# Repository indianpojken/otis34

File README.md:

# Otis34

A minimalist, not so ergonomic 34-key keyboard designed for portability.
Features a unibody layout and support for Kailh Choc V1 low-profile switches via hotswap sockets and OLED.

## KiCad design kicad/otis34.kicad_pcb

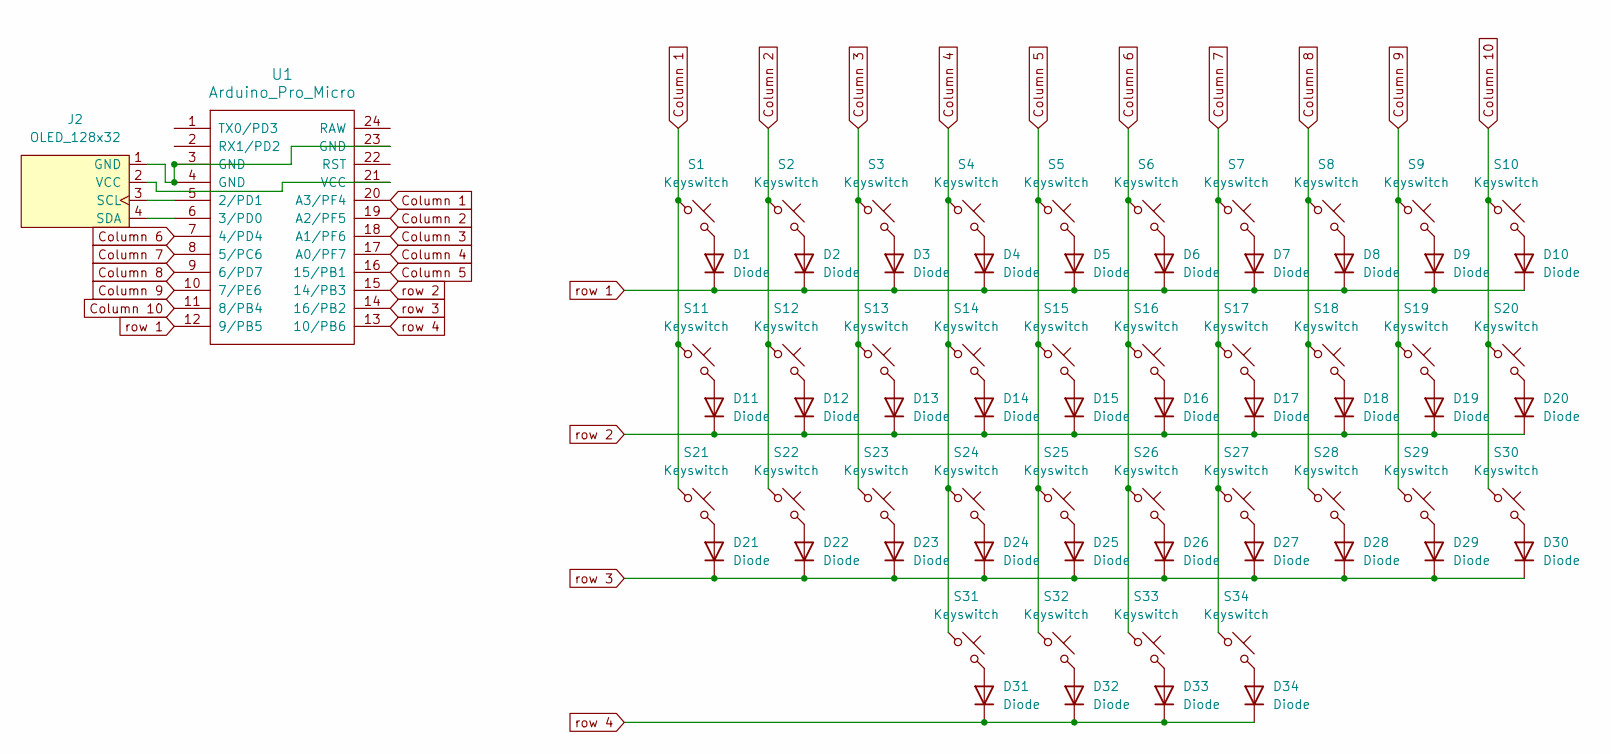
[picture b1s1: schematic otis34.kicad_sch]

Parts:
D1, D2, D3, D4, D5, D6, D7, D8, D9, D10, D11, D12, D13, D14, D15, D16, D17, D18, D19, D20, D21, D22, D23, D24, D25, D26, D27, D28, D29, D30, D31, D32, D33, D34: Diode; Diode_SOD-123
J2: OLED_128x32
S1, S2, S3, S4, S5, S6, S7, S8, S9, S10, S11, S12, S13, S14, S15, S16, S17, S18, S19, S20, S21, S22, S23, S24, S25, S26, S27, S28, S29, S30, S31, S32, S33, S34: Keyswitch; Hotswap_Choc_V1V2_1.00u
U1: Arduino_Pro_Micro

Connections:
Column 1: S1.1, S11.1, S21.1, U1.20 (A3/PF4)
Column 2: S2.1, S12.1, S22.1, U1.19 (A2/PF5)
Column 3: S3.1, S13.1, S23.1, U1.18 (A1/PF6)
Column 4: S4.1, S14.1, S24.1, S31.1, U1.17 (A0/PF7)
Column 5: S5.1, S15.1, S25.1, S32.1, U1.16 (15/PB1)
Column 6: S6.1, S16.1, S26.1, S33.1, U1.7 (4/PD4)
Column 7: S7.1, S17.1, S27.1, S34.1, U1.8 (5/PC6)
Column 8: S8.1, S18.1, S28.1, U1.9 (6/PD7)
Column 9: S9.1, S19.1, S29.1, U1.10 (7/PE6)
Column 10: S10.1, S20.1, S30.1, U1.11 (8/PB4)
unnamed: D1.2 (A), S1.2
unnamed: D2.2 (A), S2.2
unnamed: D3.2 (A), S3.2
unnamed: D4.2 (A), S4.2
unnamed: D5.2 (A), S5.2
unnamed: D6.2 (A), S6.2
unnamed: D7.2 (A), S7.2
unnamed: D8.2 (A), S8.2
unnamed: D9.2 (A), S9.2
unnamed: D10.2 (A), S10.2
unnamed: D11.2 (A), S11.2
unnamed: D12.2 (A), S12.2
unnamed: D13.2 (A), S13.2
unnamed: D14.2 (A), S14.2
unnamed: D15.2 (A), S15.2
unnamed: D16.2 (A), S16.2
unnamed: D17.2 (A), S17.2
unnamed: D18.2 (A), S18.2
unnamed: D19.2 (A), S19.2
unnamed: D20.2 (A), S20.2
unnamed: D21.2 (A), S21.2
unnamed: D22.2 (A), S22.2
unnamed: D23.2 (A), S23.2
unnamed: D24.2 (A), S24.2
unnamed: D25.2 (A), S25.2
unnamed: D26.2 (A), S26.2
unnamed: D27.2 (A), S27.2
unnamed: D28.2 (A), S28.2
unnamed: D29.2 (A), S29.2
unnamed: D30.2 (A), S30.2
unnamed: D31.2 (A), S31.2
unnamed: D32.2 (A), S32.2
unnamed: D33.2 (A), S33.2
unnamed: D34.2 (A), S34.2
unnamed: J2.1 (GND), U1.3 (GND), U1.4 (GND), U1.23 (GND)
unnamed: J2.3 (SCL), U1.5 (2/PD1)
unnamed: J2.4 (SDA), U1.6 (3/PD0)
unnamed: J2.2 (VCC), U1.21 (VCC)
row 1: D1.1 (K), D2.1 (K), D3.1 (K), D4.1 (K), D5.1 (K), D6.1 (K), D7.1 (K), D8.1 (K), D9.1 (K), D10.1 (K), U1.12 (9/PB5)
row 2: D11.1 (K), D12.1 (K), D13.1 (K), D14.1 (K), D15.1 (K), D16.1 (K), D17.1 (K), D18.1 (K), D19.1 (K), D20.1 (K), U1.15 (14/PB3)
row 3: D21.1 (K), D22.1 (K), D23.1 (K), D24.1 (K), D25.1 (K), D26.1 (K), D27.1 (K), D28.1 (K), D29.1 (K), D30.1 (K), U1.14 (16/PB2)
row 4: D31.1 (K), D32.1 (K), D33.1 (K), D34.1 (K), U1.13 (10/PB6)

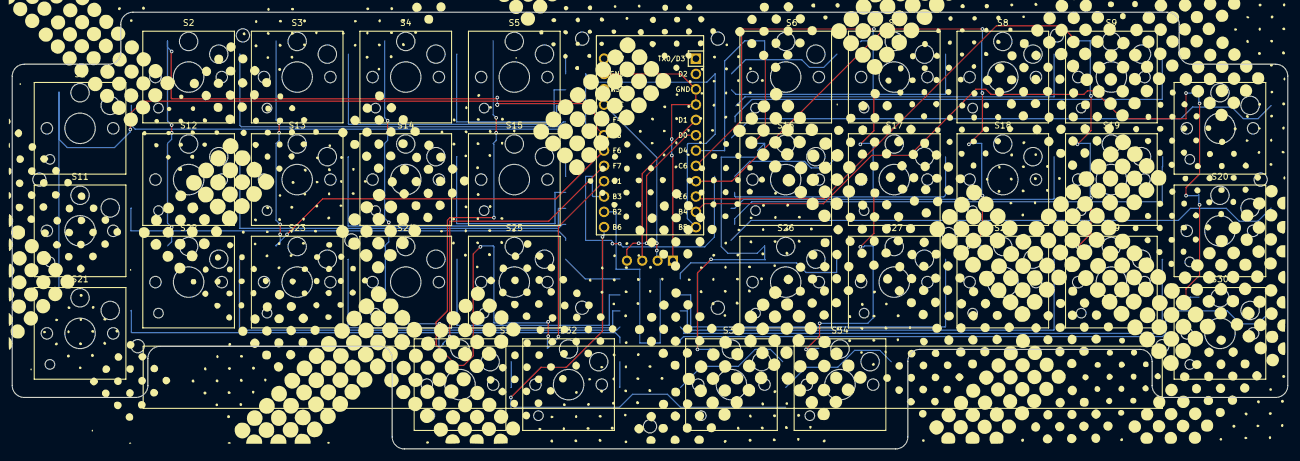
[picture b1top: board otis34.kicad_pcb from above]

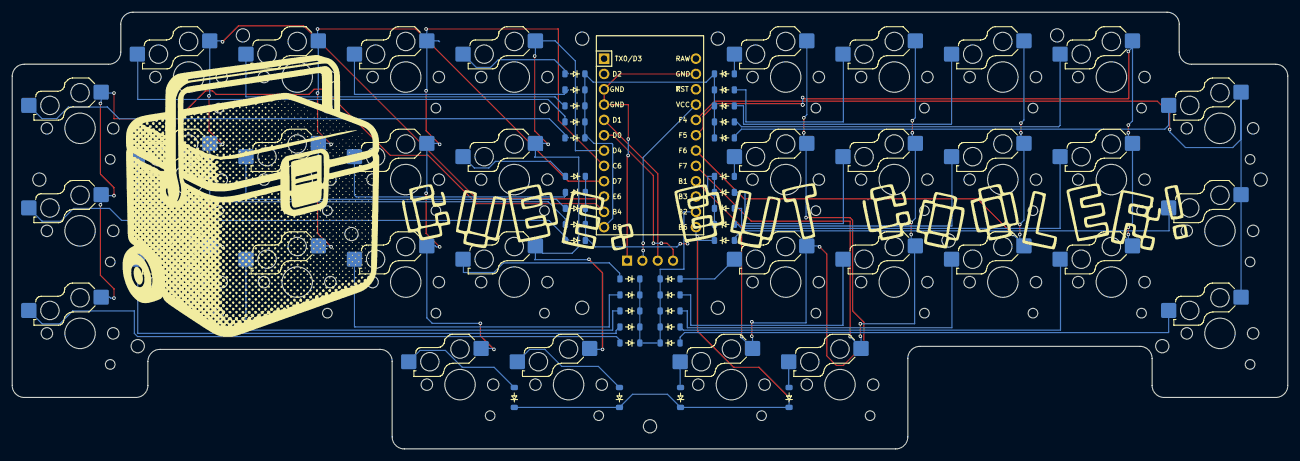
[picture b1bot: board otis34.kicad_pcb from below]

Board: 2 copper layers, 211.5 x 72.4 mm, 70 parts (35 on the bottom side), 52 nets.

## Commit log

2025-04-30 inital
2025-04-30 feat: add readme
